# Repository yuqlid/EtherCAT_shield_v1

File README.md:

# EtherCAT_shield_v1
Nuleo64 EtherCAT Board

This board connect Nucleo64 to EtherCAT with LAN9252 controller chip.

Target Nucleo64 board
- NUCLEO-L476RG http://www.st.com/ja/evaluation-tools/nucleo-l476rg.html
- NUCLEO-F446RE http://www.st.com/ja/evaluation-tools/nucleo-f446re.html

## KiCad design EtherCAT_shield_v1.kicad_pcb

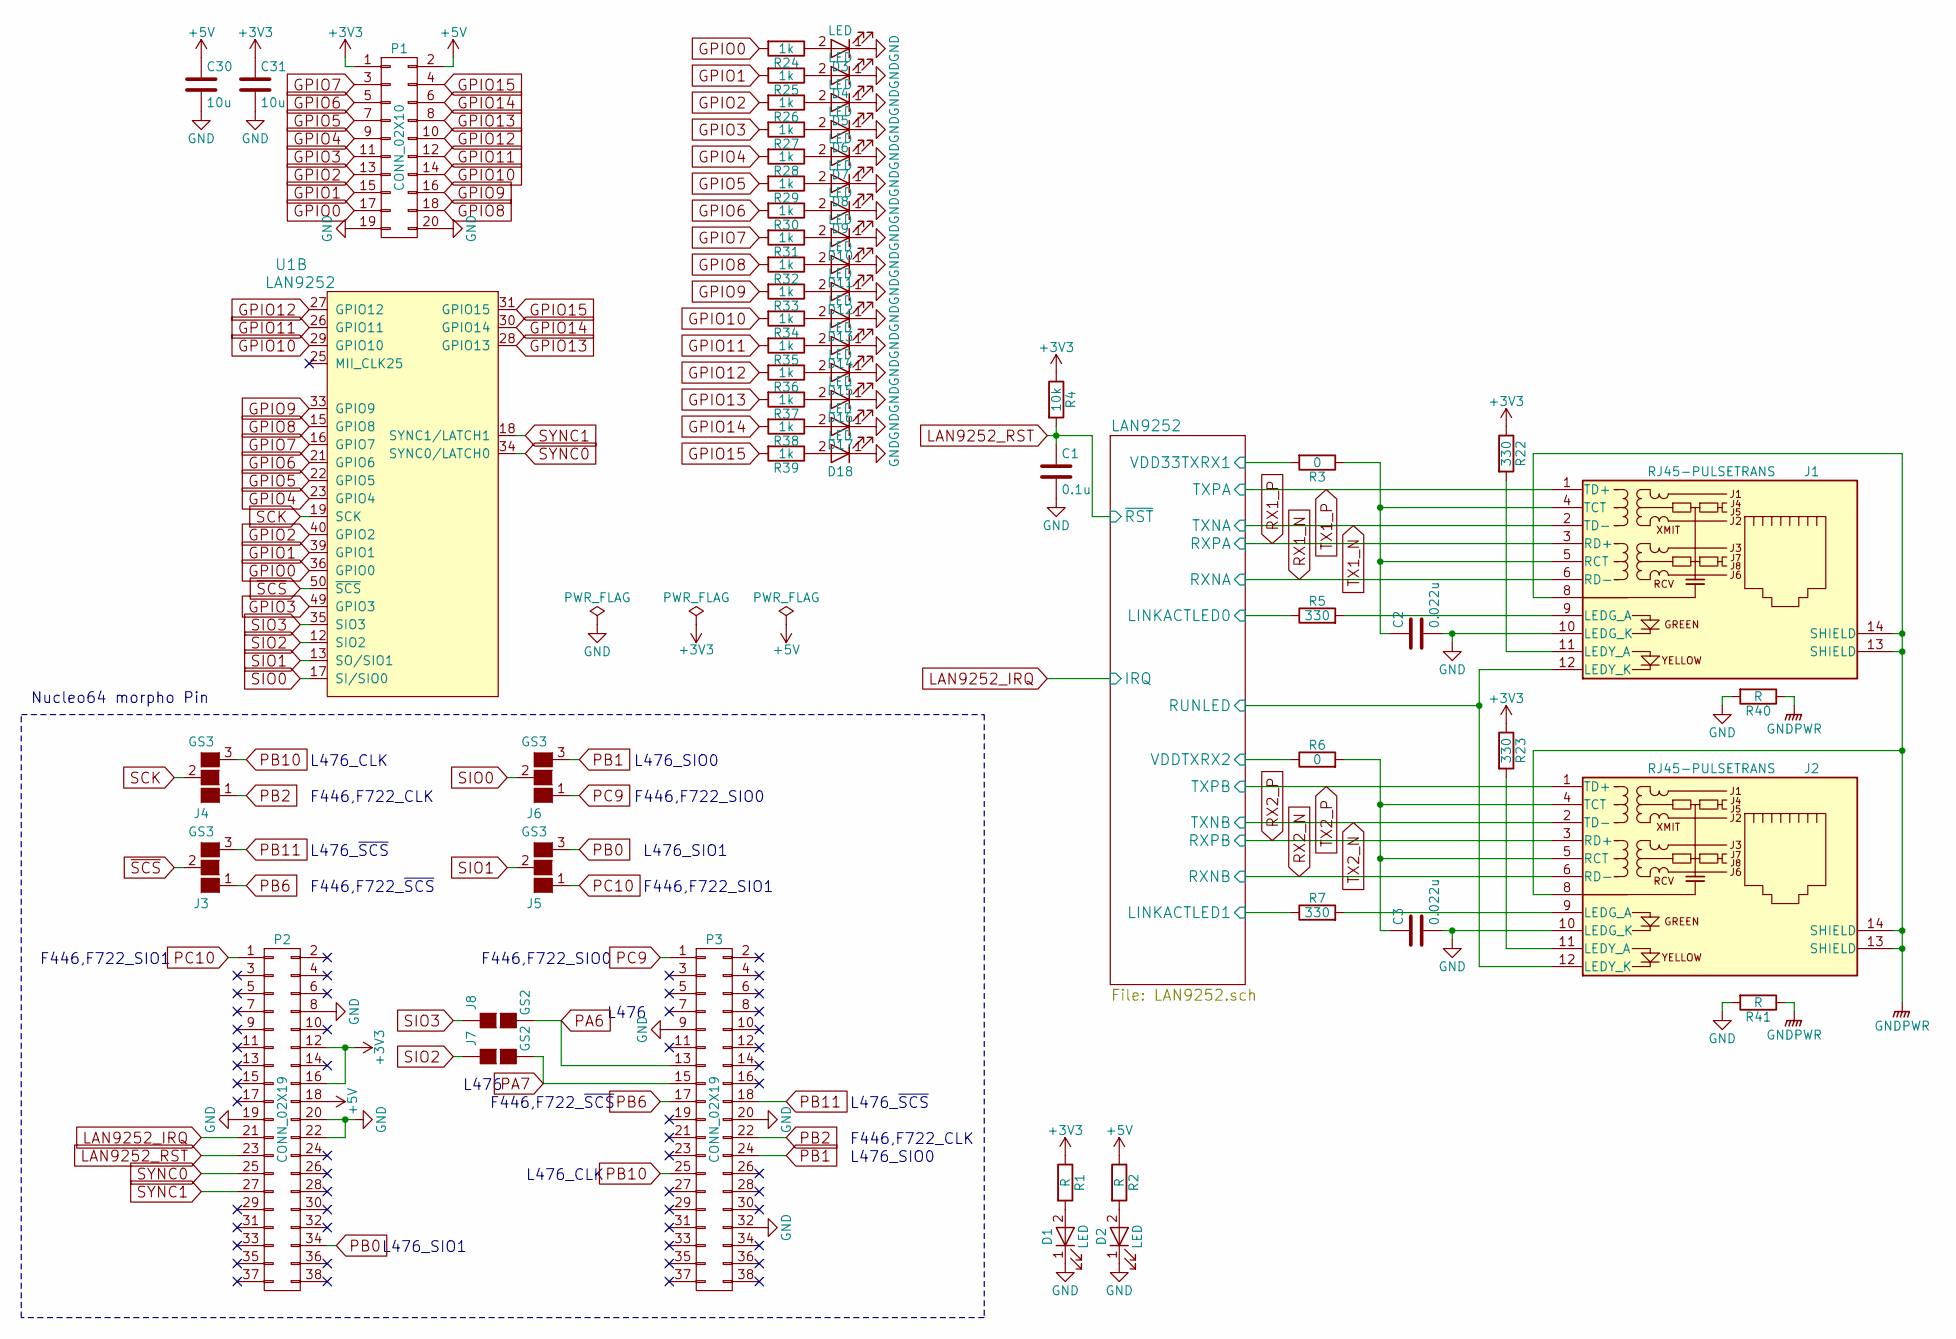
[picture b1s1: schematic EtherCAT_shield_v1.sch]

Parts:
C1: 0.1u; C_0603
C2, C3: 0.022u; C_0603
C30, C31: 10u; C_0805
D1, D2, D3, D4, D5, D6, D7, D8, D9, D10, D11, D12, D13, D14, D15, D16, D17, D18: LED; LED_0603
J1, J2: RJ45-PULSETRANS; RJ45_J0011D21BNL
J3, J4, J5, J6: GS3
J7, J8: GS2
P1: CONN_02X10; Socket_Strip_Straight_2x10_Pitch2.54mm
P2, P3: CONN_02X19; Pin_Header_Straight_2x19_Pitch2.54mm
R1, R2: R; R_0603
R3, R6: 0; R_0603
R4: 10k; R_0603
R5, R7, R22, R23: 330; R_0603
R24, R25, R26, R27, R28, R29, R30, R31, R32, R33, R34, R35, R36, R37, R38, R39: 1k; R_0603
R40, R41: R; R_1210
U1: LAN9252; QFN-64-1EP_9x9mm_Pitch0.5mm

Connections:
+3V3: C31.1, P1.1, P2.12, P2.16, R1.1, R4.1, R22.1, R23.1; also elsewhere on the board
+5V: C30.1, P1.2, P2.18, R2.1
/LAN9252/LINKACTLED0: R5.1; also elsewhere on the board
/LAN9252/LINKACTLED1: R7.1; also elsewhere on the board
/LAN9252/RUNLED: J1.12 (LEDY_K), J2.12 (LEDY_K); also elsewhere on the board
/LAN9252/VDD33TXRX1: R3.2; also elsewhere on the board
/LAN9252/VDDTXRX2: R6.1; also elsewhere on the board
GND: C1.2, C2.2, C3.2, C30.2, C31.2, D1.1 (K), D2.1 (K), D3.1 (K), D4.1 (K), D5.1 (K), D6.1 (K), D7.1 (K), D8.1 (K), D9.1 (K), D10.1 (K), D11.1 (K), D12.1 (K), D13.1 (K), D14.1 (K), D15.1 (K), D16.1 (K), D17.1 (K), D18.1 (K), J1.10 (LEDG_K), J2.10 (LEDG_K), P1.19, P1.20, P2.8, P2.19, P2.20, P2.22, P3.9, P3.20, P3.32, R40.2, R41.2; also elsewhere on the board
GNDPWR: J1.8, J1.13 (SHIELD), J1.14 (SHIELD), J2.8, J2.13 (SHIELD), J2.14 (SHIELD), R40.1, R41.1
GPIO0: P1.17, R24.2, U1.36 (GPIO0)
GPIO1: P1.15, R25.2, U1.39 (GPIO1)
GPIO2: P1.13, R26.2, U1.40 (GPIO2)
GPIO3: P1.11, R27.2, U1.49 (GPIO3)
GPIO4: P1.9, R28.2, U1.23 (GPIO4)
GPIO5: P1.7, R29.2, U1.22 (GPIO5)
GPIO6: P1.5, R30.2, U1.21 (GPIO6)
GPIO7: P1.3, R31.2, U1.16 (GPIO7)
GPIO8: P1.18, R32.2, U1.15 (GPIO8)
GPIO9: P1.16, R33.2, U1.33 (GPIO9)
GPIO10: P1.14, R34.2, U1.29 (GPIO10)
GPIO11: P1.12, R35.2, U1.26 (GPIO11)
GPIO12: P1.10, R36.2, U1.27 (GPIO12)
GPIO13: P1.8, R37.2, U1.28 (GPIO13)
GPIO14: P1.6, R38.2, U1.30 (GPIO14)
GPIO15: P1.4, R39.2, U1.31 (GPIO15)
LAN9252_IRQ: P2.21; also elsewhere on the board
LAN9252_RST: C1.1, P2.23, R4.2; also elsewhere on the board
unnamed: C2.1, J1.4 (TCT), J1.5 (RCT), R3.1
unnamed: C3.1, J2.4 (TCT), J2.5 (RCT), R6.2
unnamed: D1.2 (A), R1.2
unnamed: D2.2 (A), R2.2
unnamed: D3.2 (A), R24.1
unnamed: D4.2 (A), R25.1
unnamed: D5.2 (A), R26.1
unnamed: D6.2 (A), R27.1
unnamed: D7.2 (A), R28.1
unnamed: D8.2 (A), R29.1
unnamed: D9.2 (A), R30.1
unnamed: D10.2 (A), R31.1
unnamed: D11.2 (A), R32.1
unnamed: D12.2 (A), R33.1
unnamed: D13.2 (A), R34.1
unnamed: D14.2 (A), R35.1
unnamed: D15.2 (A), R36.1
unnamed: D16.2 (A), R37.1
unnamed: D17.2 (A), R38.1
unnamed: D18.2 (A), R39.1
unnamed: J1.9 (LEDG_A), R5.2
unnamed: J1.11 (LEDY_A), R22.2
unnamed: J2.9 (LEDG_A), R7.2
unnamed: J2.11 (LEDY_A), R23.2
PA6: J8.2 (G2), P3.13
PA7: J7.2 (G2), P3.15
PB0: J5.3 (G3), P2.34
PB1: J6.3 (G3), P3.24
PB2: J4.1 (G1), P3.22
PB6: J3.1 (G1), P3.17
PB10: J4.3 (G3), P3.25
PB11: J3.3 (G3), P3.18
PC9: J6.1 (G1), P3.1
PC10: J5.1 (G1), P2.1
RX1_N: J1.6 (RD-); also elsewhere on the board
RX1_P: J1.3 (RD+); also elsewhere on the board
RX2_N: J2.6 (RD-); also elsewhere on the board
RX2_P: J2.3 (RD+); also elsewhere on the board
SCK: J4.2 (G2), U1.19 (SCK)
SIO0: J6.2 (G2), U1.17 (SI/SIO0)
SIO1: J5.2 (G2), U1.13 (SO/SIO1)
SIO2: J7.1 (G1), U1.12 (SIO2)
SIO3: J8.1 (G1), U1.35 (SIO3)
SYNC0: P2.25, U1.34 (SYNC0/LATCH0)
SYNC1: P2.27, U1.18 (SYNC1/LATCH1)
TX1_N: J1.2 (TD-); also elsewhere on the board
TX1_P: J1.1 (TD+); also elsewhere on the board
TX2_N: J2.2 (TD-); also elsewhere on the board
TX2_P: J2.1 (TD+); also elsewhere on the board
~SCS: J3.2 (G2), U1.50 (~SCS)

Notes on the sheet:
F446,F722_~SCS
L476_CLK
L476
L476_SIO1
F446,F722_SIO1
F446,F722_CLK
L476_~SCS
L476_SIO0
F446,F722_SIO0
Nucleo64 morpho Pin

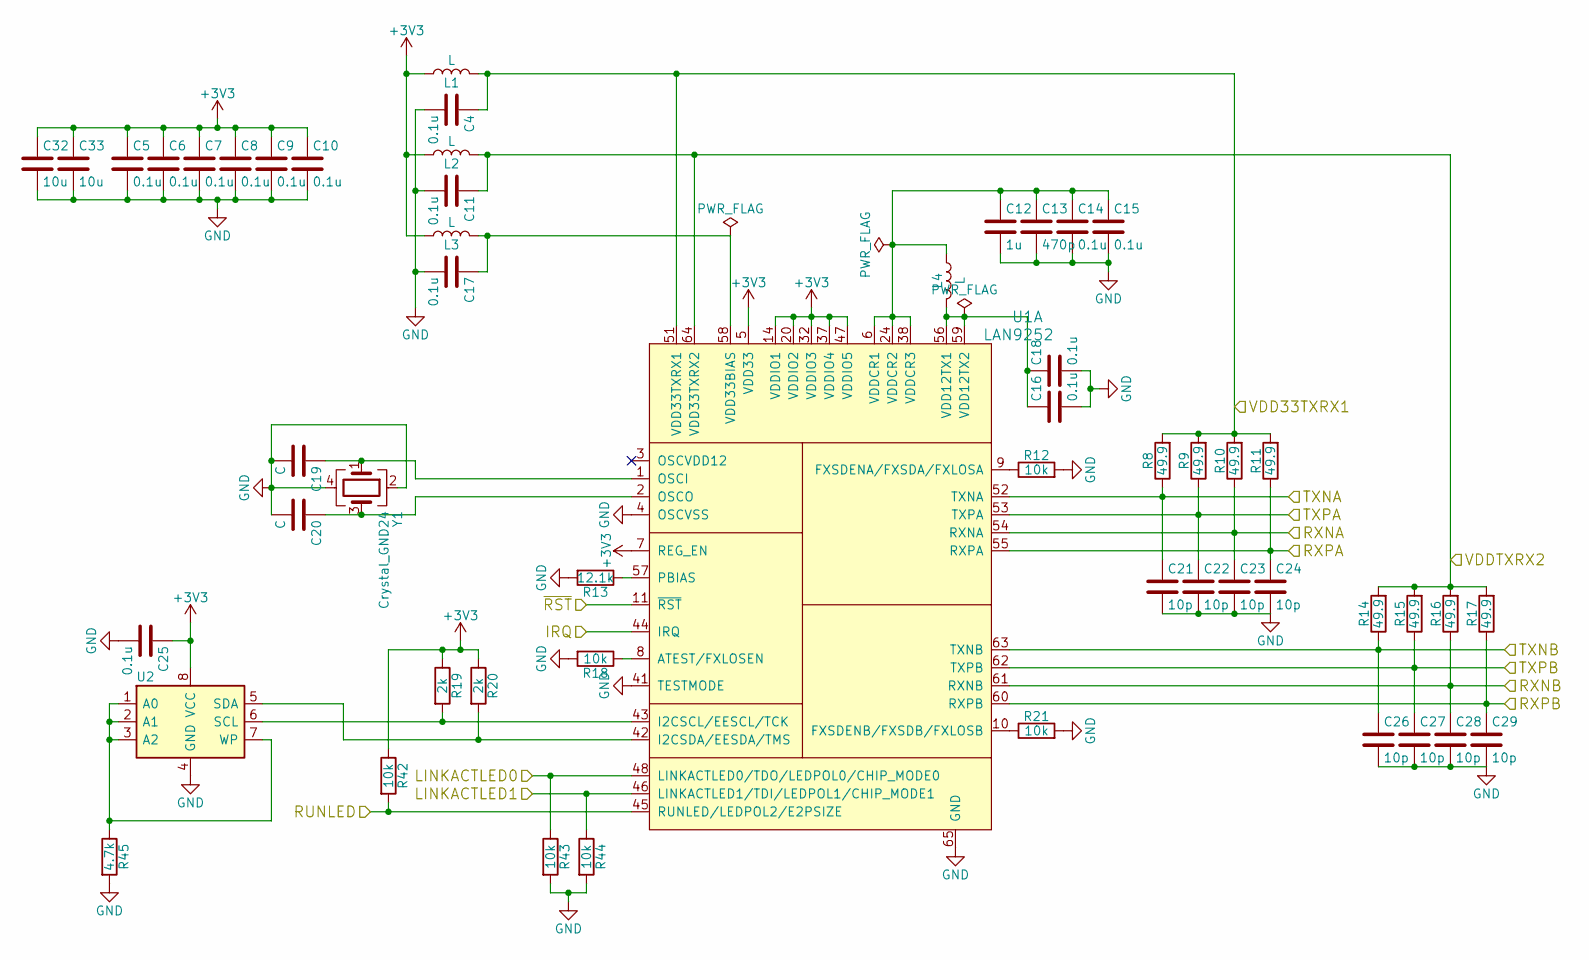
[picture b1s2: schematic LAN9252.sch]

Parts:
C4, C5, C6, C7, C8, C9, C10, C11, C14, C15, C16, C17, C18, C25: 0.1u; C_0603
C12: 1u; C_0603
C13: 470p; C_0603
C19, C20: C; C_0603
C21, C22, C23, C24, C26, C27, C28, C29: 10p; C_0603
C32, C33: 10u; C_0805
L1, L2, L3, L4: L; C_0603
R8, R9, R10, R11, R14, R15, R16, R17: 49.9; R_0603
R12, R18, R21, R42, R43, R44: 10k; R_0603
R13: 12.1k; R_0603
R19, R20: 2k; R_0603
R45: 4.7k; R_0603
U1: LAN9252; QFN-64-1EP_9x9mm_Pitch0.5mm
U2: 24LC00; DIP-8_W7.62mm_Socket_LongPads
Y1: Crystal_GND24; Crystal_SMD_Abracon_ABM8G-4pin_3.2x2.5mm

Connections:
+3V3: C5.1, C6.1, C7.1, C8.1, C9.1, C10.1, C25.1, C32.1, C33.1, L1.1, L2.1, L3.1, R19.1, R20.1, R42.1, U1.5 (VDD33), U1.7 (REG_EN), U1.14 (VDDIO1), U1.20 (VDDIO2), U1.32 (VDDIO3), U1.37 (VDDIO4), U1.47 (VDDIO5), U2.8 (VCC); also elsewhere on the board
/LAN9252/LINKACTLED0: R43.1, U1.48 (LINKACTLED0/TDO/LEDPOL0/CHIP_MODE0); also elsewhere on the board
/LAN9252/LINKACTLED1: R44.1, U1.46 (LINKACTLED1/TDI/LEDPOL1/CHIP_MODE1); also elsewhere on the board
/LAN9252/RUNLED: R42.2, U1.45 (RUNLED/LEDPOL2/E2PSIZE); also elsewhere on the board
/LAN9252/VDD33TXRX1: C4.1, L1.2, R8.2, R9.2, R10.2, R11.2, U1.51 (VDD33TXRX1); also elsewhere on the board
/LAN9252/VDDTXRX2: C11.1, L2.2, R14.2, R15.2, R16.2, R17.2, U1.64 (VDD33TXRX2); also elsewhere on the board
GND: C4.2, C5.2, C6.2, C7.2, C8.2, C9.2, C10.2, C11.2, C12.2, C13.2, C14.2, C15.2, C16.2, C17.2, C18.2, C19.2, C20.2, C21.2, C22.2, C23.2, C24.2, C25.2, C26.2, C27.2, C28.2, C29.2, C32.2, C33.2, R12.2, R13.2, R18.2, R21.2, R43.2, R44.2, R45.2, U1.4 (OSCVSS), U1.41 (TESTMODE), U1.65 (GND), U2.4 (GND), Y1.2, Y1.4; also elsewhere on the board
LAN9252_IRQ: U1.44 (IRQ); also elsewhere on the board
LAN9252_RST: U1.11 (~RST); also elsewhere on the board
unnamed: C12.1, C13.1, C14.1, C15.1, L4.1, U1.6 (VDDCR1), U1.24 (VDDCR2), U1.38 (VDDCR3)
unnamed: C16.1, C18.1, L4.2, U1.56 (VDD12TX1), U1.59 (VDD12TX2)
unnamed: C17.1, L3.2, U1.58 (VDD33BIAS)
unnamed: C19.1, U1.1 (OSCI), Y1.1
unnamed: C20.1, U1.2 (OSCO), Y1.3
unnamed: R12.1, U1.9 (FXSDENA/FXSDA/FXLOSA)
unnamed: R13.1, U1.57 (PBIAS)
unnamed: R18.1, U1.8 (ATEST/FXLOSEN)
unnamed: R19.2, U1.43 (I2CSCL/EESCL/TCK), U2.6 (SCL)
unnamed: R20.2, U1.42 (I2CSDA/EESDA/TMS), U2.5 (SDA)
unnamed: R21.1, U1.10 (FXSDENB/FXSDB/FXLOSB)
unnamed: R45.1, U2.1 (A0), U2.2 (A1), U2.3 (A2), U2.7 (WP)
RX1_N: C23.1, R10.1, U1.54 (RXNA); also elsewhere on the board
RX1_P: C24.1, R11.1, U1.55 (RXPA); also elsewhere on the board
RX2_N: C28.1, R16.1, U1.61 (RXNB); also elsewhere on the board
RX2_P: C29.1, R17.1, U1.60 (RXPB); also elsewhere on the board
TX1_N: C21.1, R8.1, U1.52 (TXNA); also elsewhere on the board
TX1_P: C22.1, R9.1, U1.53 (TXPA); also elsewhere on the board
TX2_N: C26.1, R14.1, U1.63 (TXNB); also elsewhere on the board
TX2_P: C27.1, R15.1, U1.62 (TXPB); also elsewhere on the board

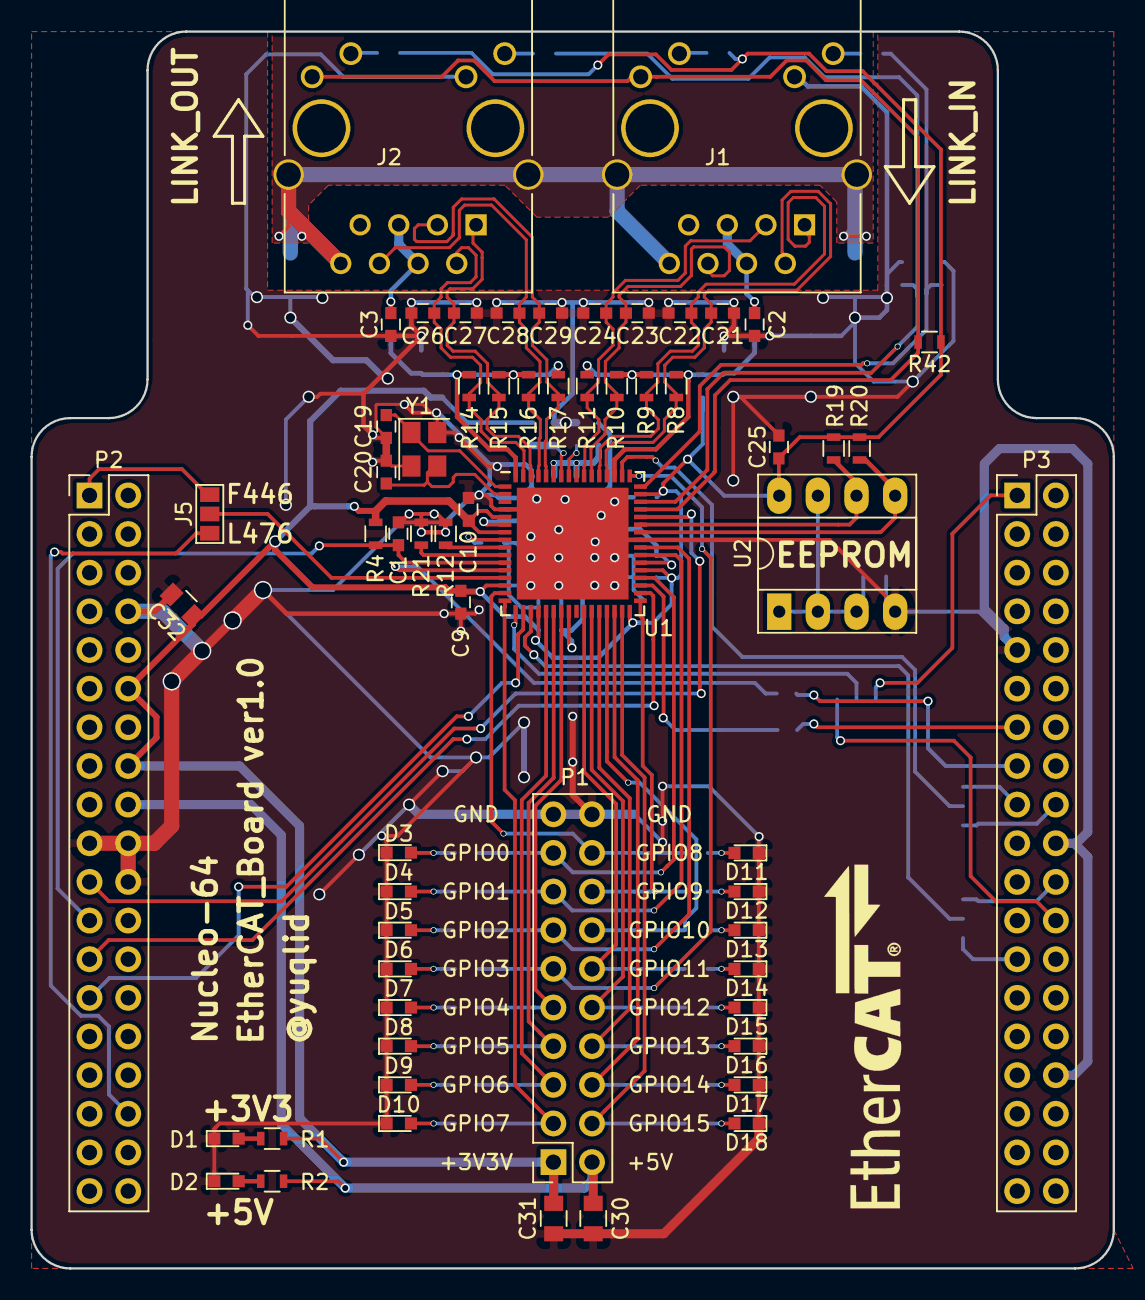
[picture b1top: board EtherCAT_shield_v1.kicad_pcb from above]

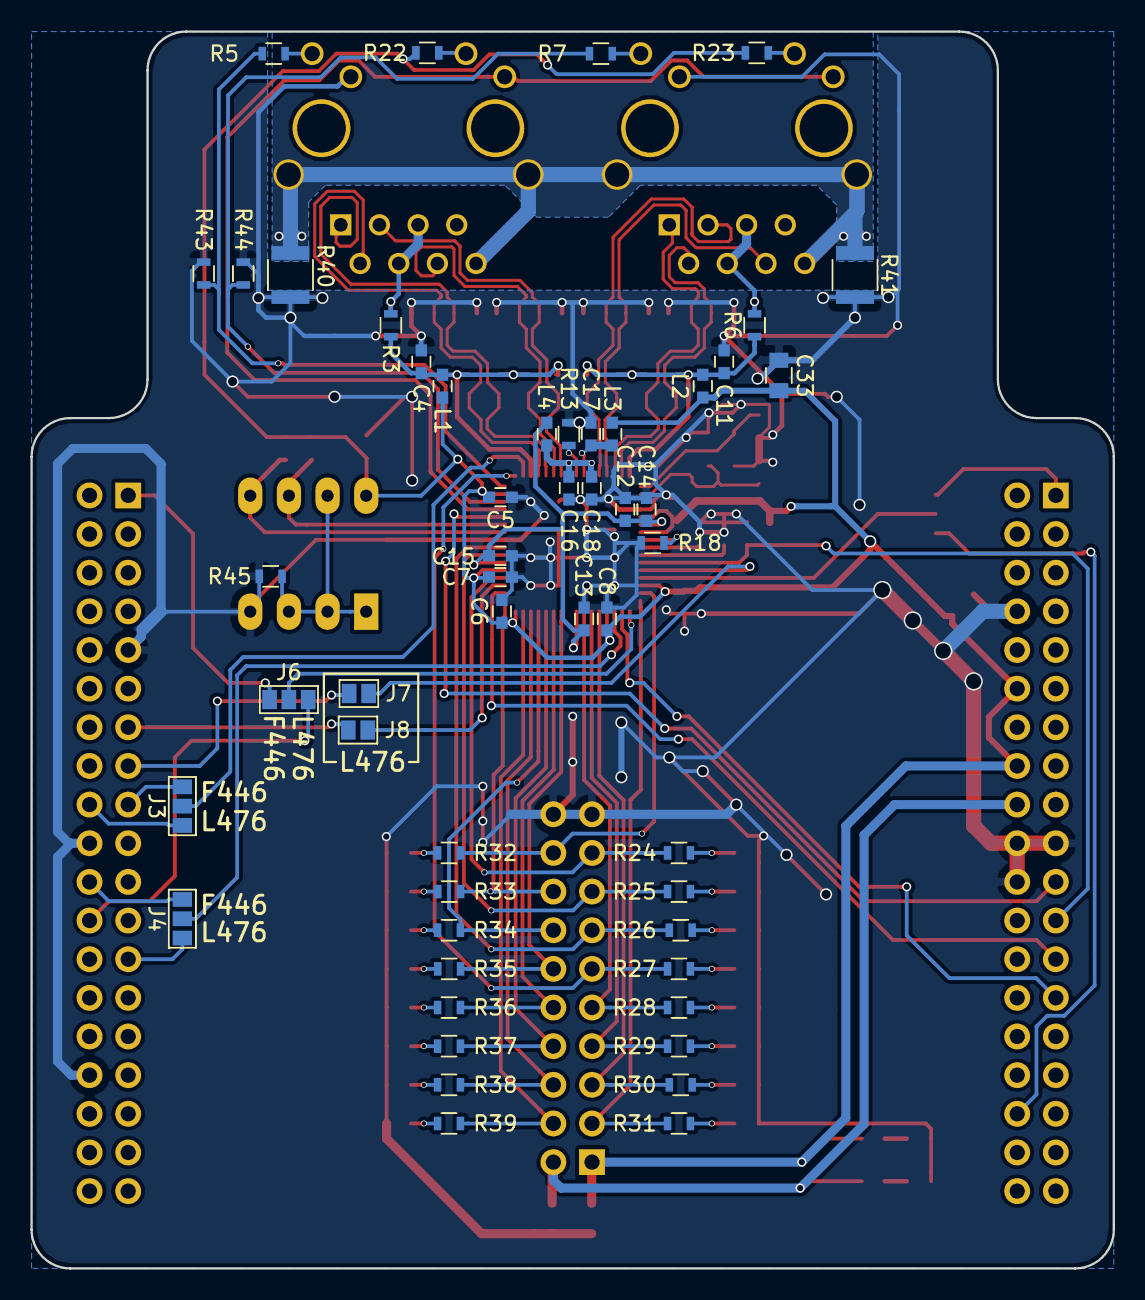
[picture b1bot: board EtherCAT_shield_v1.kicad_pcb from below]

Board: 2 copper layers, 71.1 x 81.3 mm, 114 parts (52 on the bottom side), 89 nets.

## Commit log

2017-03-27 Initial_commit
2017-03-27 部品修正．一度アノテーションとネットリスト生成
2017-03-28 ピンソケットの位置合わせ
2017-03-28 適当に外形起こした
2017-03-28 部品変更，再アノテーション，コネクタだけ配置
2017-03-29 差動線修正
2017-03-29 LINK方向の矢印追加
2017-03-29 画像はりたい
2017-03-29 ロゴ追加した
2017-03-30 LED変更，再アノテーション
2017-04-02 GPIOのLED並べた 実質完成
2017-04-02 外形を変更
2017-04-02 外形線を変更
2017-04-02 回路図を整理した
2017-04-03 外形寸法を書いた
2017-04-03 CHS GNDとPCB GNDを抵抗で接続
2017-04-03 GNDまわりの調整
2017-04-03 抵抗とかコンデンサを追加
2017-04-06 viaの調整
2017-04-06 このデータで発注します
2017-04-06 ドリルデータをミスってた＆マスク出し忘れてたのでこっちで発注
2017-04-07 値ふってBOM作成
2017-04-08 BOM更新
2017-04-23 C16が未接続だったので修正
2017-04-23 C11のシルクの位置を修正
2017-04-23 LINK_IN,LINK_OUTの向きを修正
2017-05-11 部品のURLを修正
2017-05-12 不要な製造ファイルを削除
2017-05-18 PDF追加
2017-06-03 RJ45コネクタののLED向きを修正
2017-06-03 pdf回路図を更新
